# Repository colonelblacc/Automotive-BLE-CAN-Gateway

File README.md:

# Automotive BLE-to-CAN Hardware Gateway
### Connected Vehicle Telematics & High-Speed CAN FD Interface Module

<div align="center">

-gold)
-blue)
-red)

<br>

| Top View (BLE 5.3 SoC, RF Front-End, Test Points) | Bottom View (Automotive Power Conditioning & Battery) |
| :---: | :---: |
|  |  |

</div>

---

## About the Project

Modern vehicles and commercial fleets produce a wealth of diagnostics and telemetry over internal CAN networks. Accessing and logging that data wirelessly—without bulky external dongles or unreliable power taps—can be a challenge. 

I designed this 4-layer hardware gateway to bridge **CAN Flexible Data-Rate (CAN FD)** networks directly to **Bluetooth Low Energy (BLE 5.3)**. It allows mobile devices, diagnostic tablets, or edge gateways to monitor real-time vehicle telemetry, capture OBD-II/UDS data frames, and stream sensor feeds over a secure wireless connection.

The hardware is built specifically for automotive environments:
- **Wide Input Range (9V–36V):** Runs directly from 12V passenger cars or 24V commercial vehicle batteries.
- **Harsh Electrical Protection:** Protected against reverse polarity, load dump transients, and ESD spikes up to ±30kV on the CAN bus.
- **Seamless Battery Backup:** On-board Li-ion battery backup with automatic hardware switchover (<2 µs failover) ensures uninterrupted logging even when vehicle power cuts out during engine cranking or battery disconnects.

---

## Key Hardware Specifications

| Subsystem | Component / Specification | Key Details |
| :--- | :--- | :--- |
| **Wireless SoC** | **TI CC2340R52E0RKPR** | 48 MHz Arm Cortex-M0+, 512 KB Flash, 36 KB SRAM, BLE 5.3 radio |
| **CAN Controller** | **TI TCAN4550-Q1** | Integrated CAN FD controller & transceiver, up to 5 Mbps, AEC-Q100 Grade 1 |
| **Primary Buck** | **TI LM5164** | 100V wide-input synchronous buck regulator delivering 3.3V logic power |
| **Battery Management**| **TI BQ24040 + TPS63900** | Linear single-cell Li-ion charger with thermal foldback + high-efficiency buck-boost |
| **Power Multiplexer**| **TI TPS2116** | Automatic hardware priority power mux (<2 µs break-before-make switchover) |
| **CAN Supply** | **TI LMR36506** | Dedicated 65V/0.6A synchronous buck providing isolated ~6.0V to CAN transceiver |
| **Reverse Protection**| **Vishay SQ2361AEES** | -60V P-channel MOSFET (dissipates <15 mW under full load) |
| **Overvoltage / ESD** | **Littelfuse SMAJ36CA + Nexperia ESDCAN24** | 36V 400W TVS clamp + ±30kV automotive CAN bus ESD suppressors |
| **RF Front-End** | **Johanson 2450AT18D0100E** | 2.45 GHz ceramic chip antenna with 50Ω CPWG feed and discrete Pi matching |
| **PCB Technology** | **4-Layer FR4 (~1.6mm)** | JLC04161H stackup (1 oz outer / 0.5 oz inner Cu, ENIG finish) |

---

## System Architecture & Power Distribution

The power tree is split intentionally into separate regulators to isolate noisy loads (like CAN bus transceivers) from sensitive high-frequency digital logic and the BLE radio.

<div align="center">
  
</div>

```
┌────────────────────────────────────────────────────────────────────────────────────────┐
│                        9V-36V Vehicle Power Input (J1)                                 │
│  F1 (2A Fuse) ──► D1 (36V TVS) ──► Q1 (P-FET Reverse Clamp) ──► VIN_PROTECTED          │
└────────────────────────────────────────┬───────────────────────────────────────────────┘
                                         │
              ┌──────────────────────────┼──────────────────────────┐
              ▼                          ▼                          ▼
    ┌──────────────────┐       ┌──────────────────┐       ┌──────────────────┐
    │  U1: LM5164      │       │  U4: LMR36506    │       │  U8: LMR36506    │
    │  100V→3.3V Buck  │       │  65V→5V Buck     │       │  65V→6V Buck     │
    │  (3V3_REG)       │       │  (5V_CHARGER)    │       │  (VSUP_CAN)      │
    └─────────┬────────┘       └─────────┬────────┘       └─────────┬────────┘
              │                          ▼                          │
              │                 ┌──────────────────┐                │
              │                 │  U5: BQ24040     │                │
              │                 │  Li-Ion Charger  │                │
              │                 └────────┬─────────┘                │
              │                          ▼                          │
              │                 ┌──────────────────┐                │
              │                 │  J_BAT1 Li-Ion   │                │
              │                 │  3.7V / 4.2V     │                │
              │                 └────────┬─────────┘                │
              │                          ▼                          │
              │                 ┌──────────────────┐                │
              │                 │  U6: TPS63900    │                │
              │                 │  Buck-Boost      │                │
              │                 │  (3V3_BAT)       │                │
              │                 └────────┬─────────┘                │
              │                          │                          │
              ▼ (IN1: Priority)          ▼ (IN2: Backup)            │
    ┌──────────────────────────────────────────────┐                │
    │  U7: TPS2116 Power Mux (<2µs Failover)       │                │
    └──────────────────────┬───────────────────────┘                │
                           ▼                                        │
                 +3.3V System Bus                                   │
              ┌────────────┴────────────┐                           │
              ▼                         ▼                           ▼
    ┌──────────────────┐      ┌──────────────────┐        ┌──────────────────┐
    │  U2: CC2340R52   │◄────►│  U3: TCAN4550-Q1 │◄───────│  CAN FD Bus (J2) │
    │  Arm Cortex-M0+  │ SPI  │  CAN FD Controller│       │  Differential Tx │
    │  BLE 5.3 SoC     │      │  & Transceiver   │        │  ISO 11898-2     │
    └──────────────────┘      └──────────────────┘        └──────────────────┘
```

---

## Schematic Walkthrough

The project is structured in KiCad 10 across 5 hierarchical sheets to keep functional blocks clean, modular, and easy to review.

<details open>
<summary><b>🔍 Click to expand/collapse schematic sheets</b></summary>
<br>

### Root Hierarchical Sheet
Connects the top-level power rails, high-speed SPI bus, CAN differential pairs, and control lines between sheets.

---

### Sheet 01: Vehicle Power Conditioning & LM5164 Wide-VIN Buck (9V–36V)
Handles incoming vehicle power protection: 2A fuse, bidirectional 36V TVS clamp, reverse-polarity P-FET switch, and the high-voltage LM5164 buck converter stepping down to 3.3V logic.

---

### Sheet 02: TI CC2340R52 BLE 5.3 MCU & 50Ω CPWG RF Matching
Features the TI CC2340R52 SoC, decoupling network, crystal oscillators, 50Ω Coplanar Waveguide with Ground (CPWG), discrete Pi matching filter, and ceramic chip antenna with ground keepout.

---

### Sheet 03: TI TCAN4550-Q1 CAN FD Controller & Dedicated Power Stage
Houses the TCAN4550-Q1 CAN FD controller, high-speed SPI interface, common-mode choke (ACT45B), ±30kV ESD clamp, jumper-selectable split termination (JP1), and the dedicated 6V buck supply (U8).

---

### Sheet 04: Li-Ion Battery Charger & Automatic Power Mux
Contains the BQ24040 linear charging IC with NTC thermal foldback, TPS63900 buck-boost regulator (3.3V output from single cell 3.0V–4.2V), and TPS2116 priority power multiplexer for seamless battery failover.

---

### Sheet 05: Connectors & SWD Debug Header
Automotive terminal headers for vehicle power, CAN bus, battery JST connection, and standard SWD/JTAG debug pins for firmware flashing.

</details>

---

## 4-Layer PCB Stackup & Layout

The board uses a standard 4-layer stackup (**JLC04161H-7628**) with 1 oz copper outer layers and 0.5 oz inner layers (~1.6 mm finished thickness, ENIG surface finish).

<div align="center">

| Layer 1: Front Copper (F.Cu - RF CPWG & High-Speed Signals) | Layer 2: Inner Ground (In1.Cu - Solid Ground Plane) |
| :---: | :---: |
|  |  |
| **Layer 3: Inner Power (In2.Cu - Power Polygons)** | **Layer 4: Bottom Copper (B.Cu - Low-Speed Signals & GND)** |
|  |  |

</div>

| Layer | Type | Copper | Function & Routing Strategy |
| :--- | :--- | :---: | :--- |
| **L1 (Top)** | Signal | 1 oz (35 µm) | 50Ω CPWG RF feed to chip antenna, high-speed SPI lines, IC placement |
| **L2 (Inner 1)**| Ground | 0.5 oz (17.5 µm)| **Solid unbroken ground plane** directly under RF and differential CAN pairs |
| **L3 (Inner 2)**| Power | 0.5 oz (17.5 µm)| Star power distribution (+3.3V system, 3V3_BAT, 5V_CHARGER, VSUP_CAN) |
| **L4 (Bottom)** | Signal/GND | 1 oz (35 µm) | Battery charger circuitry, power passives, low-speed status traces, ground flood |

---

## Key Design Decisions & Why I Made Them

1. **P-Channel MOSFET vs. Schottky Diode for Reverse Polarity:**  
   At 1.5A transient load, a typical Schottky diode has a forward drop of 0.4V–0.6V, wasting over 600 mW as heat in an enclosed casing. I used an AEC-Q101 qualified P-MOSFET (Vishay SQ2361AEES, -60V Vds). Its low on-resistance (~30 mΩ) keeps power dissipation below **15 mW**, eliminating heatsink requirements entirely.

2. **Dedicated CAN Transceiver Buck Stage (U8):**  
   CAN transceivers draw sharp, high-current pulses during dominant bit transitions. Powering the TCAN4550 transceiver directly from the primary 3.3V logic rail could cause voltage sag or couple high-frequency switching hash into the BLE radio. A dedicated 6V buck (U8) isolates transceiver noise from the rest of the board.

3. **Hardware Power Mux (TPS2116) vs. Diode-OR:**  
   Simple dual-diode OR circuits suffer from diode voltage drops and battery leakage. The TPS2116 power multiplexer provides seamless break-before-make transition with an ultra-fast **<2 µs switchover time**. Vehicle power (IN1) is given strict priority; if it drops below threshold, the multiplexer instantly switches to battery backup without resetting the MCU.

4. **Split AC Termination on CAN Bus (JP1):**  
   Instead of a single 120Ω resistor across CAN_H and CAN_L, I implemented split termination using two 60.4Ω precision resistors with a center-tapped 4.7nF capacitor to ground. This filters common-mode RF noise without impacting differential signals. A jumper header allows configuring the board as an end-of-line (120Ω) or mid-bus node.

---

## Verification & Sign-Off

The board layout and electrical connectivity were verified in KiCad with **zero errors and zero warnings**:

<div align="center">

| Design Rule Check (DRC: 0 Errors / 0 Warnings) | Electrical Rules Check (ERC: 0 Errors / 0 Warnings) |
| :---: | :---: |
|  |  |

</div>

- **Minimum Track Width:** 0.20 mm (8 mil) — well within standard fabrication capability
- **Minimum Clearance:** 0.20 mm (8 mil)
- **Via Drill / Pad:** 0.30 mm drill / 0.60 mm pad
- **RF 50Ω CPWG Trace:** 0.35 mm trace with 0.15 mm ground clearance

---

## Repository Structure

```
├── Automotive_BLE_CAN.kicad_pro      # KiCad 10.0 project configuration
├── Automotive_BLE_CAN.kicad_sch      # Top-level hierarchical schematic
├── Automotive_BLE_CAN.kicad_pcb      # 4-layer PCB layout
├── 01_Power_Input.kicad_sch          # Sheet 1: Power conditioning & buck
├── 02_BLE_MCU.kicad_sch              # Sheet 2: CC2340R52 BLE SoC & RF matching
├── 03_CAN_Interface.kicad_sch        # Sheet 3: TCAN4550-Q1 CAN FD interface
├── 04_Battery.kicad_sch              # Sheet 4: Battery charger & power mux
├── 05_Connectors_Debug.kicad_sch     # Sheet 5: Connectors & SWD header
│
├── Architecture Diagram/             # Block diagram & architecture drawing
│   ├── Automotive_BLE_CAN_Architecture_Diagram.png
│   └── Automotive_BLE_CAN_Architecture_Diagram.pdf
│
├── BOM/                              # Bill of Materials
│   └── BOM_Automotive_BLE_CAN.csv    # Full component procurement list (73 line items)
│
├── Gerbers/                          # Production RS-274X manufacturing files
│   ├── Automotive_BLE_CAN-F_Cu.gtl   # Top Copper
│   ├── Automotive_BLE_CAN-In1_Cu.g1  # Layer 2 Ground Plane
│   ├── Automotive_BLE_CAN-In2_Cu.g2  # Layer 3 Power Polygons
│   ├── Automotive_BLE_CAN-B_Cu.gbl   # Bottom Copper
│   └── ...                           # Soldermasks, silkscreens, edge cuts
│
├── Drill File/                       # Excellon NC drill files
│   ├── Automotive_BLE_CAN.drl
│   └── Automotive_BLE_CAN-drl.rpt
│
├── Schematics/                       # Schematic vector export
│   └── Automotive_BLE_CAN.pdf        # Complete multi-sheet schematic PDF
│
├── Step Files/                       # 3D mechanical model
│   └── Automotive_BLE_CAN.step       # 3D STEP AP214 CAD assembly
│
│
├── COMPONENT_SELECTION_AND_CALCULATIONS.md # Component selection & design calculations
├── LICENSE                           # MIT License
└── README.md                         # Project documentation
```

---

## How to View the Project

1. **Install KiCad 10** (or KiCad 8/9 with compatible import).
2. Clone this repository:
   ```bash
   git clone https://github.com/colonelblacc/Automotive-BLE-CAN-Gateway.git
   ```
3. Open `Automotive_BLE_CAN.kicad_pro` in KiCad.
4. Open the schematic editor to inspect the hierarchical sheets, or the PCB editor to view the 4-layer routing and 3D viewer (`Alt+3`).
5. Gerbers in `Gerbers/` can be previewed directly using **KiCad GerbView** or online tools like JLCPCB/PCBWay viewer.

---

## Author & Contact

**Ajith Shajan**  
B.Tech in Electronics and Communication Engineering  
Govt. Model Engineering College, Kochi (KTU)  
- **Email:** [ajithshajan.mec@gmail.com](mailto:ajithshajan.mec@gmail.com)  
- **LinkedIn:** [linkedin.com/in/ajith-shajan-a33745295](https://linkedin.com/in/ajith-shajan-a33745295)  
- **GitHub:** [@colonelblacc](https://github.com/colonelblacc)

---

## License

This project is open-source hardware licensed under the [MIT License](LICENSE).

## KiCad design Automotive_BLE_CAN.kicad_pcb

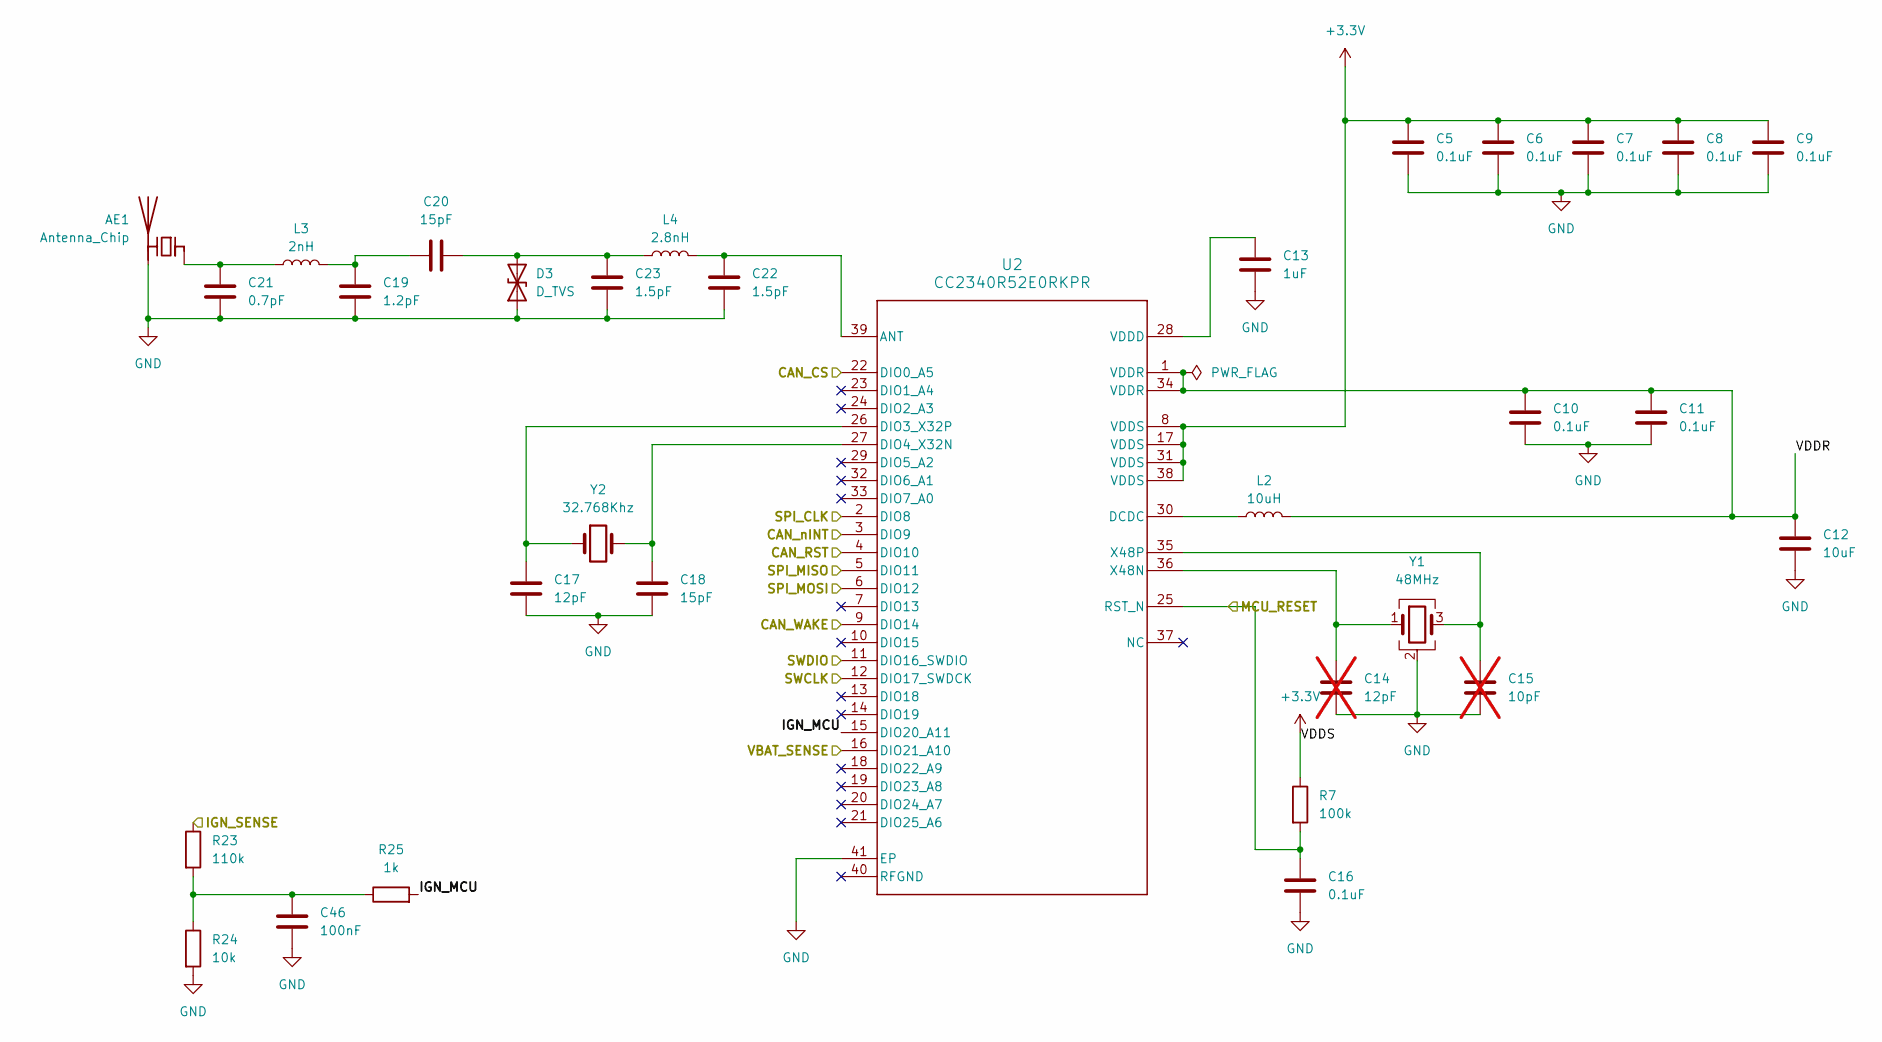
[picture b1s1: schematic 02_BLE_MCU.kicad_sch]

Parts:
AE1: Antenna_Chip; Johanson_2450AT18x100_2400-2500Mhz
C5, C6, C7, C8, C9, C10, C11, C16: 0.1uF; C_0603_1608Metric
C12: 10uF; C_0603_1608Metric
C13: 1uF; C_0603_1608Metric
C14: 12pF; C_0402_1005Metric; not fitted
C15: 10pF; C_0402_1005Metric; not fitted
C17: 12pF; C_0402_1005Metric
C18, C20: 15pF; C_0402_1005Metric
C19: 1.2pF; C_0402_1005Metric
C21: 0.7pF; C_0402_1005Metric
C22, C23: 1.5pF; C_0402_1005Metric
C46: 100nF; C_0603_1608Metric
D3: D_TVS; D_0402_1005Metric
L2: 10uH; L_0805_2012Metric
L3: 2nH; L_0402_1005Metric
L4: 2.8nH; L_0402_1005Metric
R7: 100k; R_0603_1608Metric
R23: 110k; R_0603_1608Metric
R24: 10k; R_0603_1608Metric
R25: 1k; R_0603_1608Metric
U2: CC2340R52E0RKPR; RKP0040B-MFG
Y1: 48MHz; Crystal_SMD_2016-4Pin_2.0x1.6mm
Y2: 32.768Khz; Crystal_SMD_3215-2Pin_3.2x1.5mm

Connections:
+3.3V: C5.1, C6.1, C7.1, C8.1, C9.1, R7.1, U2.8 (VDDS), U2.17 (VDDS), U2.31 (VDDS), U2.38 (VDDS); also elsewhere on the board
/01_Power_Input/IGN_SENSE: R23.1; also elsewhere on the board
/02_BLE_MCU/<NO NET>: C16.1, R7.2, U2.4 (DIO10), U2.25 (RST_N); also elsewhere on the board
/02_BLE_MCU/CAN_CS: U2.22 (DIO0_A5); also elsewhere on the board
/02_BLE_MCU/CAN_WAKE: U2.9 (DIO14); also elsewhere on the board
/02_BLE_MCU/CAN_nINT: U2.3 (DIO9); also elsewhere on the board
/02_BLE_MCU/IGN_MCU: R25.2, U2.15 (DIO20_A11)
/02_BLE_MCU/SPI_CLK: U2.2 (DIO8); also elsewhere on the board
/02_BLE_MCU/SPI_MISO: U2.5 (DIO11); also elsewhere on the board
/02_BLE_MCU/SPI_MOSI: U2.6 (DIO12); also elsewhere on the board
/02_BLE_MCU/SWCLK: U2.12 (DIO17_SWDCK); also elsewhere on the board
/02_BLE_MCU/SWDIO: U2.11 (DIO16_SWDIO); also elsewhere on the board
/02_BLE_MCU/VBAT_SENSE: U2.16 (DIO21_A10); also elsewhere on the board
/02_BLE_MCU/VDDR: C10.1, C11.1, C12.1, L2.2, U2.1 (VDDR), U2.34 (VDDR)
GND: AE1.2 (PCB_Trace), C5.2, C6.2, C7.2, C8.2, C9.2, C10.2, C11.2, C12.2, C13.2, C14.2, C15.2, C16.2, C17.2, C18.2, C19.2, C21.2, C22.2, C23.2, C46.2, D3.1 (A1), R24.2, U2.41 (EP), Y1.2 (G), Y1.4 (G); also elsewhere on the board
unnamed: AE1.1 (FEED), C21.1, L3.1
unnamed: C19.1, C20.1, L3.2
unnamed: C46.1, R23.2, R24.1, R25.1
unnamed: C20.2, C23.1, D3.2 (A2), L4.1
unnamed: C22.1, L4.2, U2.39 (ANT)
unnamed: L2.1, U2.30 (DCDC)
unnamed: C17.1, U2.26 (DIO3_X32P), Y2.1
unnamed: C18.1, U2.27 (DIO4_X32N), Y2.2
unnamed: C13.1, U2.28 (VDDD)
unnamed: C14.1, U2.36 (X48N), Y1.1
unnamed: C15.1, U2.35 (X48P), Y1.3

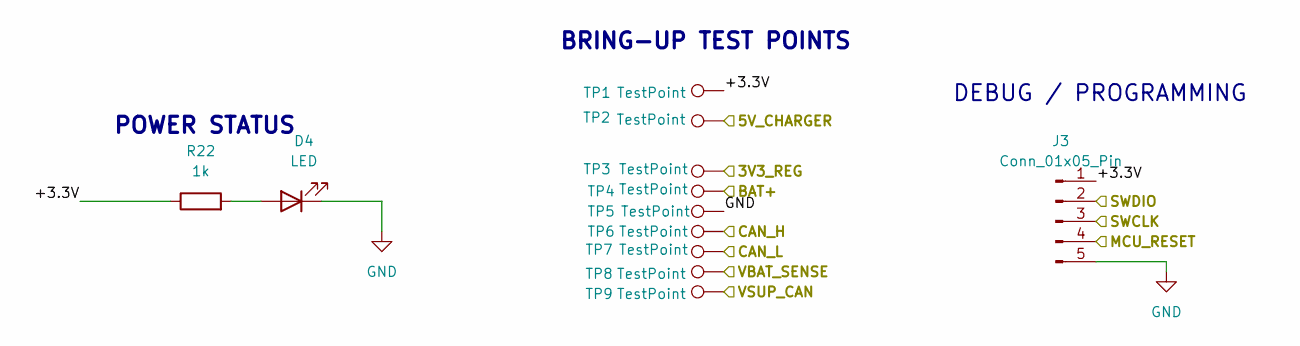
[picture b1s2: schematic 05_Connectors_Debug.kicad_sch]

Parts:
D4: LED; LED_0603_1608Metric
J3: Conn_01x05_Pin; PinHeader_1x05_P2.54mm_Vertical
R22: 1k; R_0603_1608Metric
TP1, TP2, TP3, TP4, TP5, TP6, TP7, TP8, TP9: TestPoint; TestPoint_Pad_D2.0mm

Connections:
/01_Power_Input/3V3_REG: TP3.1 (1_1); also elsewhere on the board
/02_BLE_MCU/<NO NET>: J3.4; also elsewhere on the board
/02_BLE_MCU/SWCLK: J3.3; also elsewhere on the board
/02_BLE_MCU/SWDIO: J3.2; also elsewhere on the board
/02_BLE_MCU/VBAT_SENSE: TP8.1 (1_1); also elsewhere on the board
/03_CAN_Interface/CAN_H: TP6.1 (1_1); also elsewhere on the board
/03_CAN_Interface/CAN_L: TP7.1 (1_1); also elsewhere on the board
/03_CAN_Interface/VSUP_CAN: TP9.1 (1_1); also elsewhere on the board
/04_Battery/5V_CHARGER: TP2.1 (1_1); also elsewhere on the board
/04_Battery/BAT+: TP4.1 (1_1); also elsewhere on the board
/05_Connectors_Debug/+3.3V: J3.1, R22.1, TP1.1 (1_1)
GND: D4.1 (K), J3.5, TP5.1 (1_1); also elsewhere on the board
unnamed: D4.2 (A), R22.2

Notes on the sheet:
DEBUG / PROGRAMMING
POWER STATUS
BRING-UP TEST POINTS

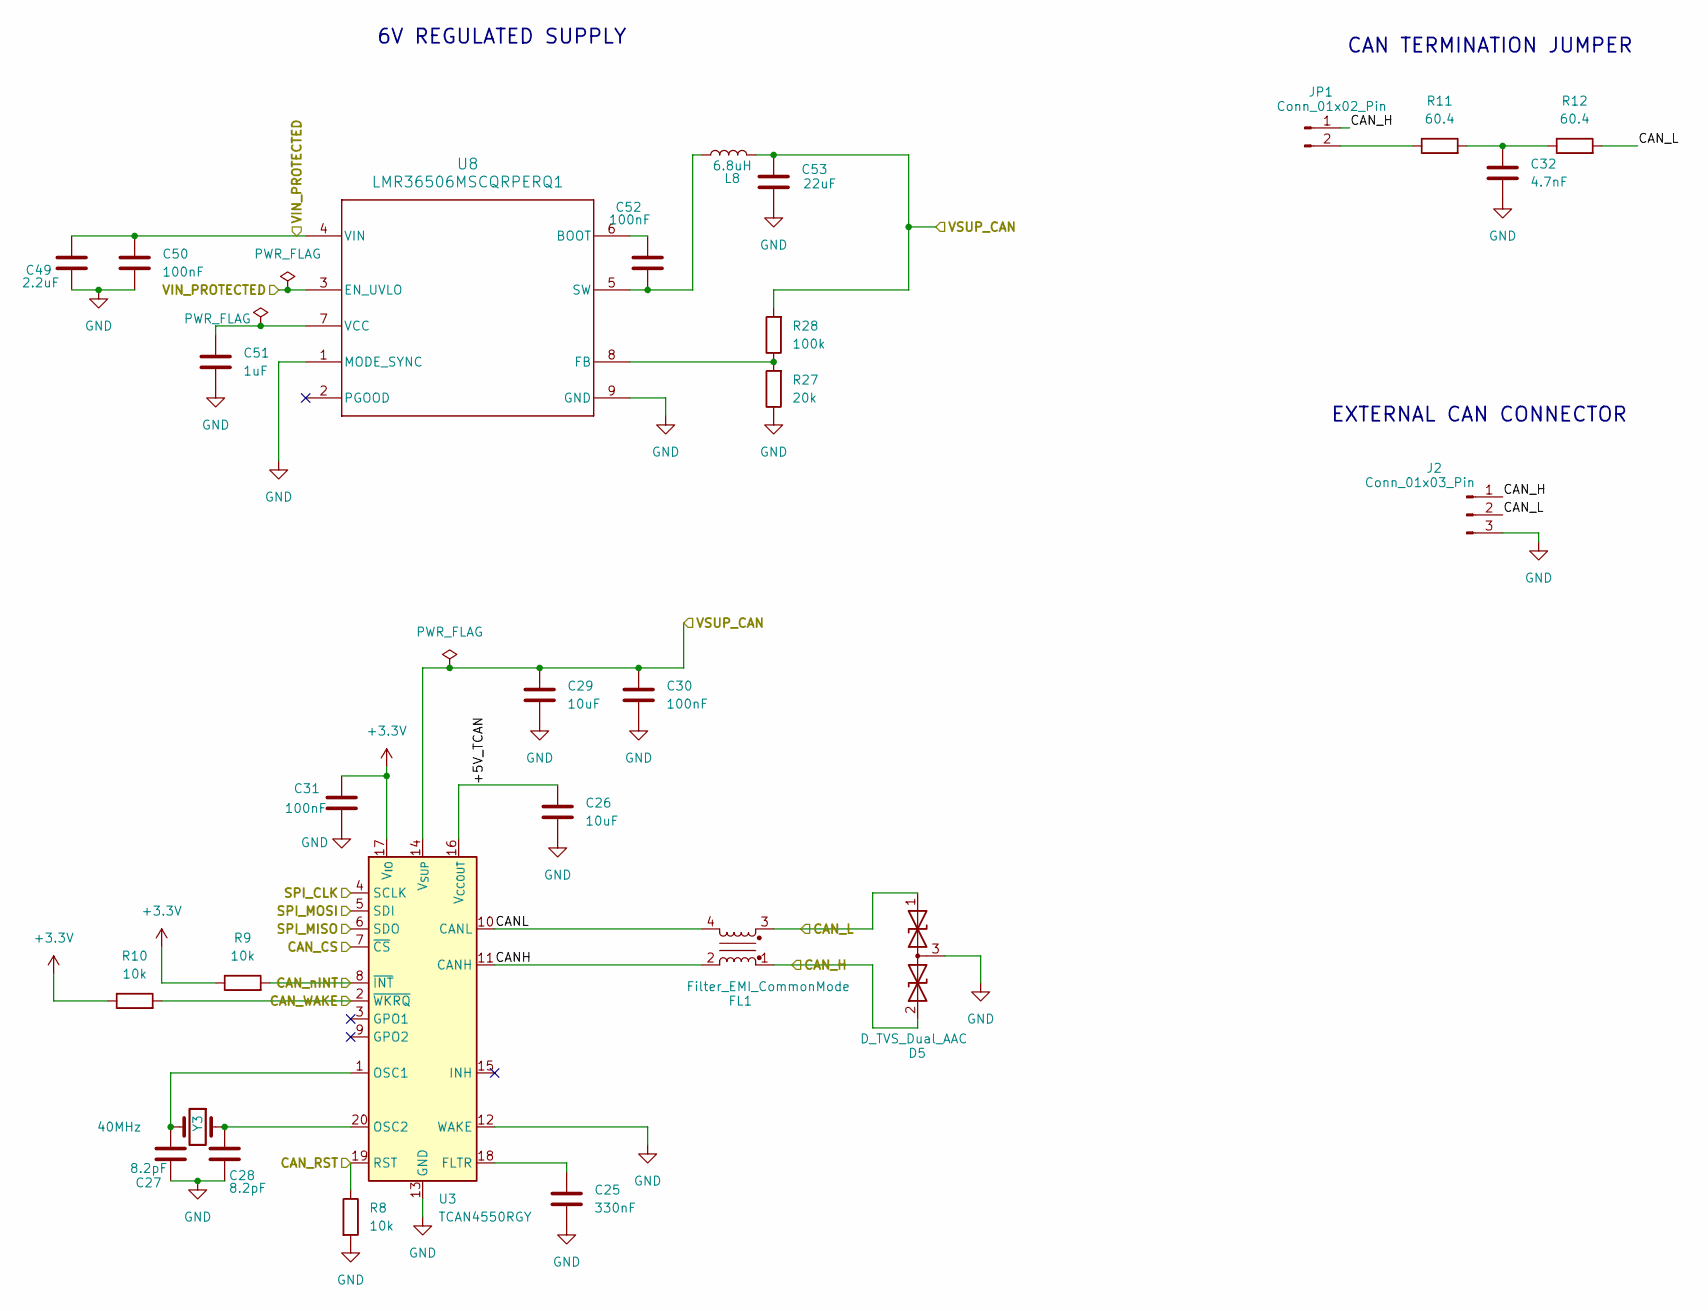
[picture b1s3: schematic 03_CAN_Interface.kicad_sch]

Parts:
C25: 330nF; C_0603_1608Metric
C26: 10uF; C_0805_2012Metric
C27, C28: 8.2pF; C_0402_1005Metric
C29: 10uF; C_1210_3225Metric
C30, C31, C50, C52: 100nF; C_0603_1608Metric
C32: 4.7nF; C_0603_1608Metric
C49: 2.2uF; C_0805_2012Metric
C51: 1uF; C_0603_1608Metric
C53: 22uF; C_0603_1608Metric
D5: D_TVS_Dual_AAC; SOT-23
FL1: Filter_EMI_CommonMode; L_CommonModeChoke_Coilcraft_1812CAN
J2: Conn_01x03_Pin; PinHeader_1x03_P2.54mm_Vertical
JP1: Conn_01x02_Pin; PinHeader_1x02_P2.54mm_Vertical
L8: 6.8uH; L_Coilcraft_XxL4020
R8, R9, R10: 10k; R_0603_1608Metric
R11, R12: 60.4; R_0805_2012Metric
R27: 20k; R_0805_2012Metric
R28: 100k; R_0805_2012Metric
U3: TCAN4550RGY; Texas_RGY_R-PVQFN-N20_EP2.05x3.05mm
U8: LMR36506MSCQRPERQ1; RPE0009A
Y3: 40MHz; Crystal_SMD_3225-4Pin_3.2x2.5mm

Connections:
+3.3V: C31.1, R9.1, R10.1, U3.17 (V_{IO}); also elsewhere on the board
/01_Power_Input/VIN_PROTECTED: C49.1, C50.1, U8.3 (EN_UVLO), U8.4 (VIN); also elsewhere on the board
/02_BLE_MCU/<NO NET>: R8.1, U3.19 (RST); also elsewhere on the board
/02_BLE_MCU/CAN_CS: U3.7 (~CS); also elsewhere on the board
/02_BLE_MCU/CAN_WAKE: R10.2, U3.2 (~WKRQ); also elsewhere on the board
/02_BLE_MCU/CAN_nINT: R9.2, U3.8 (~INT); also elsewhere on the board
/02_BLE_MCU/SPI_CLK: U3.4 (SCLK); also elsewhere on the board
/02_BLE_MCU/SPI_MISO: U3.6 (SDO); also elsewhere on the board
/02_BLE_MCU/SPI_MOSI: U3.5 (SDI); also elsewhere on the board
/03_CAN_Interface/+5V_TCAN: C26.1, U3.16 (V_{CCOUT})
/03_CAN_Interface/CANH: FL1.2, U3.11 (CANH)
/03_CAN_Interface/CANL: FL1.4, U3.10 (CANL)
/03_CAN_Interface/CAN_H: D5.2 (A2), FL1.1, J2.1, JP1.1; also elsewhere on the board
/03_CAN_Interface/CAN_L: D5.1 (A1), FL1.3, J2.2, R12.2; also elsewhere on the board
/03_CAN_Interface/VSUP_CAN: C29.1, C30.1, C53.1, L8.2, R28.2, U3.14 (V_{SUP}); also elsewhere on the board
GND: C25.2, C26.2, C27.2, C28.2, C29.2, C30.2, C31.2, C32.2, C49.2, C50.2, C51.2, C53.2, D5.3 (common), J2.3, R8.2, R27.1, U3.12 (WAKE), U3.13 (GND), U3.21 (GND), U8.1 (MODE_SYNC), U8.9 (GND); also elsewhere on the board
unnamed: C32.1, R11.2, R12.1
unnamed: JP1.2, R11.1
unnamed: C25.1, U3.18 (FLTR)
unnamed: C27.1, U3.1 (OSC1), Y3.2
unnamed: C28.1, U3.20 (OSC2), Y3.1
unnamed: C52.1, U8.6 (BOOT)
unnamed: R27.2, R28.1, U8.8 (FB)
unnamed: C52.2, L8.1, U8.5 (SW)
unnamed: C51.1, U8.7 (VCC)

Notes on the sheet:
CAN TERMINATION JUMPER
EXTERNAL CAN CONNECTOR
6V REGULATED SUPPLY

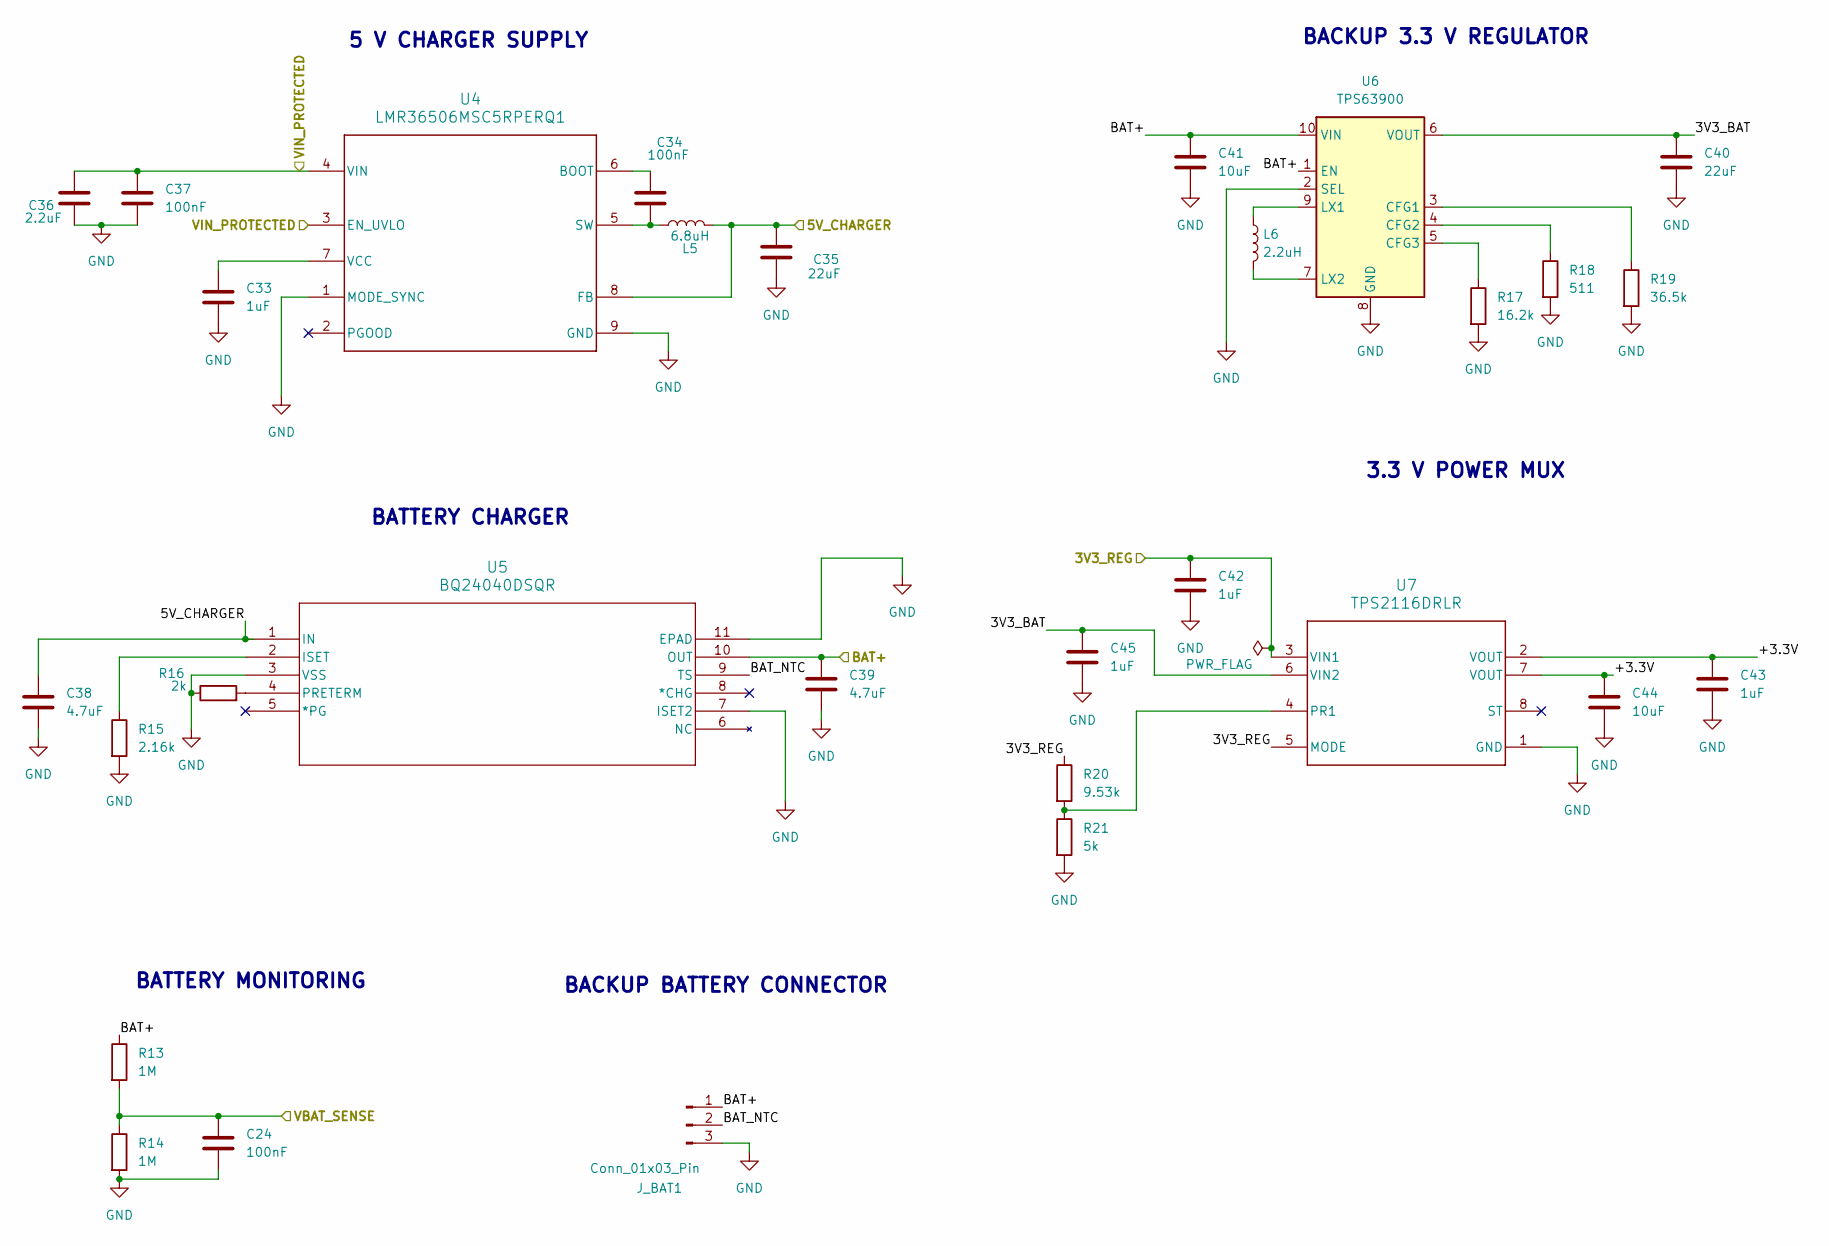
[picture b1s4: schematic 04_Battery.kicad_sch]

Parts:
C24: 100nF; C_0402_1005Metric
C33, C42, C43, C45: 1uF; C_0603_1608Metric
C34, C37: 100nF; C_0603_1608Metric
C35, C40: 22uF; C_0805_2012Metric
C36: 2.2uF; C_0805_2012Metric
C38, C39: 4.7uF; C_0805_2012Metric
C41, C44: 10uF; C_0805_2012Metric
J_BAT1: Conn_01x03_Pin; JST_PH_B3B-PH-K_1x03_P2.00mm_Vertical
L5: 6.8uH; L_Coilcraft_XxL4020
L6: 2.2uH; L_1008_2520Metric
R13, R14: 1M; R_0603_1608Metric
R15: 2.16k; R_0603_1608Metric
R16: 2k; R_0603_1608Metric
R17: 16.2k; R_0603_1608Metric
R18: 511; R_0603_1608Metric
R19: 36.5k; R_0603_1608Metric
R20: 9.53k; R_0603_1608Metric
R21: 5k; R_0603_1608Metric
U4: LMR36506MSC5RPERQ1; RPE0009A
U5: BQ24040DSQR; DSQ10_P9X1P5
U6: TPS63900; WSON-10-1EP_2.5x2.5mm_P0.5mm_EP1.2x2mm_ThermalVias
U7: TPS2116DRLR; DRL0008A-MFG

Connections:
/01_Power_Input/3V3_REG: C42.1, R20.1, U7.3 (VIN1), U7.5 (MODE); also elsewhere on the board
/01_Power_Input/VIN_PROTECTED: C36.1, C37.1, U4.3 (EN_UVLO), U4.4 (VIN); also elsewhere on the board
/02_BLE_MCU/VBAT_SENSE: C24.1, R13.2, R14.1; also elsewhere on the board
/04_Battery/3V3_BAT: C40.1, C45.1, U6.6 (VOUT), U7.6 (VIN2)
/04_Battery/5V_CHARGER: C35.1, C38.1, L5.2, U4.8 (FB), U5.1 (IN); also elsewhere on the board
/04_Battery/+3.3V: C43.1, C44.1, U7.2 (VOUT), U7.7 (VOUT)
/04_Battery/BAT+: C39.1, C41.1, J_BAT1.1, R13.1, U5.10 (OUT), U6.1 (EN), U6.10 (VIN); also elsewhere on the board
/04_Battery/BAT_NTC: J_BAT1.2, U5.9 (TS)
GND: C24.2, C33.2, C35.2, C36.2, C37.2, C38.2, C39.2, C40.2, C41.2, C42.2, C43.2, C44.2, C45.2, J_BAT1.3, R14.2, R15.2, R16.1, R17.2, R18.2, R19.2, R21.2, U4.1 (MODE_SYNC), U4.9 (GND), U5.3 (VSS), U5.7 (ISET2), U5.11 (EPAD), U6.2 (SEL), U6.8 (GND), U6.11 (GND), U7.1 (GND); also elsewhere on the board
unnamed: C34.1, U4.6 (BOOT)
unnamed: C34.2, L5.1, U4.5 (SW)
unnamed: C33.1, U4.7 (VCC)
unnamed: R15.1, U5.2 (ISET)
unnamed: R16.2, U5.4 (PRETERM)
unnamed: R19.1, U6.3 (CFG1)
unnamed: R18.1, U6.4 (CFG2)
unnamed: R17.1, U6.5 (CFG3)
unnamed: L6.1, U6.9 (LX1)
unnamed: L6.2, U6.7 (LX2)
unnamed: R20.2, R21.1, U7.4 (PR1)

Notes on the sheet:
3.3 V POWER MUX
BACKUP BATTERY CONNECTOR
BACKUP 3.3 V REGULATOR
BATTERY MONITORING
BATTERY CHARGER
5 V CHARGER SUPPLY

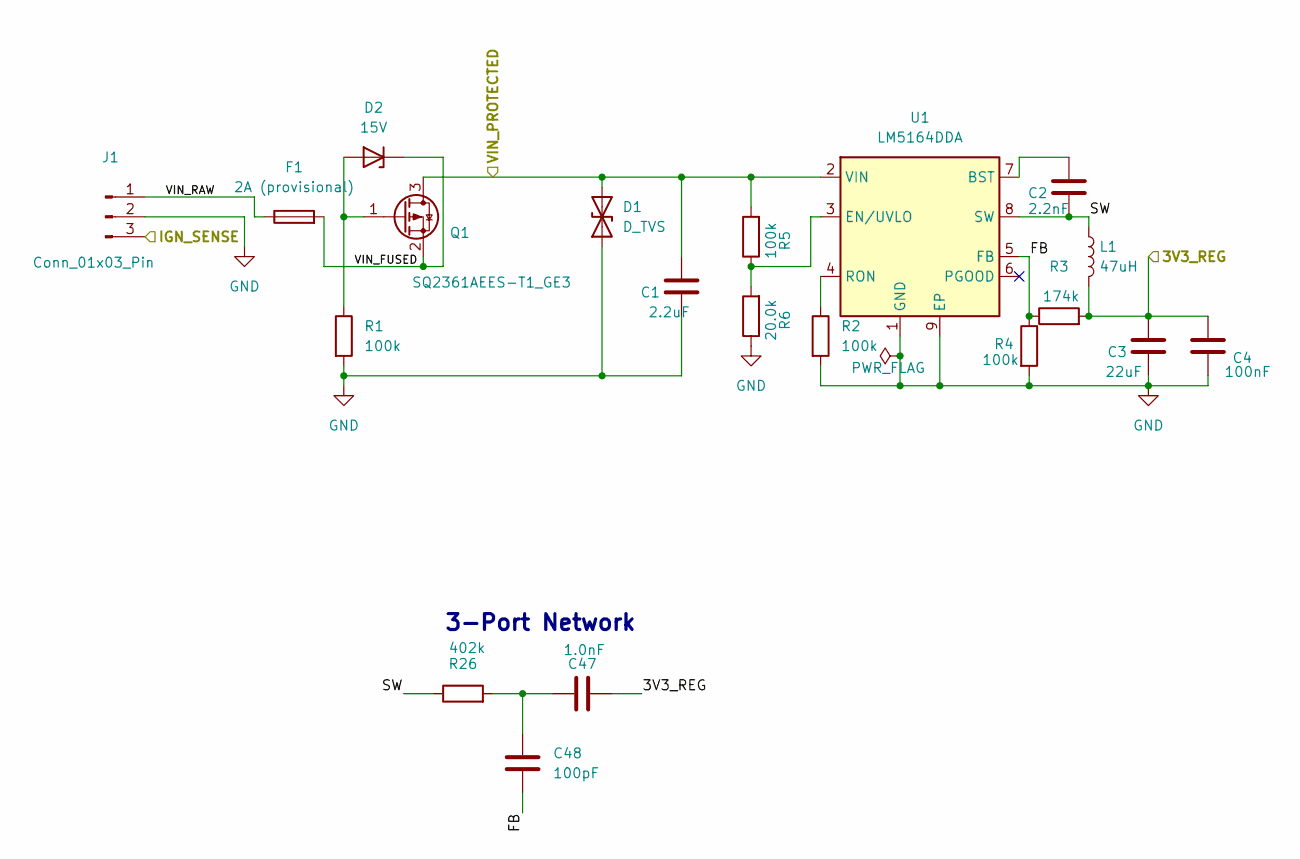
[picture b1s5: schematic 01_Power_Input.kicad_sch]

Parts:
C1: 2.2uF; C_0603_1608Metric
C2: 2.2nF; C_0603_1608Metric
C3: 22uF; C_0603_1608Metric
C4: 100nF; C_0603_1608Metric
C47: 1.0nF; C_0603_1608Metric
C48: 100pF; C_0402_1005Metric
D1: D_TVS; D_SMC
D2: 15V; D_SOD-123
F1: 2A (provisional); Fuse_1206_3216Metric
J1: Conn_01x03_Pin; PinHeader_1x03_P2.54mm_Vertical
L1: 47uH; L_Bourns_SRN6045TA
Q1: SQ2361AEES-T1_GE3; SOT-23
R1, R2, R4, R5: 100k; R_0603_1608Metric
R3: 174k; R_0603_1608Metric
R6: 20.0k; R_0603_1608Metric
R26: 402k; R_0603_1608Metric
U1: LM5164DDA; HSOP-8-1EP_3.9x4.9mm_P1.27mm_EP2.41x3.1mm_ThermalVias

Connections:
/01_Power_Input/3V3_REG: C3.1, C4.1, C47.2, L1.2, R3.2; also elsewhere on the board
/01_Power_Input/FB: C48.2, R3.1, R4.1, U1.5 (FB)
/01_Power_Input/IGN_SENSE: J1.3; also elsewhere on the board
/01_Power_Input/SW: C2.2, L1.1, R26.1, U1.8 (SW)
/01_Power_Input/VIN_FUSED: D2.1 (K), F1.2, Q1.2 (S)
/01_Power_Input/VIN_PROTECTED: C1.1, D1.2 (A2), Q1.3 (D), R5.2, U1.2 (VIN); also elsewhere on the board
/01_Power_Input/VIN_RAW: F1.1, J1.1
GND: C1.2, C3.2, C4.2, D1.1 (A1), J1.2, R1.2, R2.2, R4.2, R6.1, U1.1 (GND), U1.9 (EP); also elsewhere on the board
unnamed: C47.1, C48.1, R26.2
unnamed: D2.2 (A), Q1.1 (G), R1.1
unnamed: C2.1, U1.7 (BST)
unnamed: R5.1, R6.2, U1.3 (EN/UVLO)
unnamed: R2.1, U1.4 (RON)

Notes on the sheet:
3-Port Network
